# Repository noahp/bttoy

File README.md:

bttoy
=====
Bluetooth robot toy.

Parts
=====
1A/40V schottky  
http://www.mouser.com/ProductDetail/AVX/SD1206T040S1R0/?qs=sGAEpiMZZMtQ8nqTKtFS%2fB%252bvZQIExTNLVUxpicOfnng%3d

47uF electrolytic, 5x5.2mm  
http://www.mouser.com/ProductDetail/Lelon/VE-470M1CTR-0505/?qs=sGAEpiMZZMvwFf0viD3Y3dptsVif%2fXhRiPinzX%2fdZgo%3d

inductor  
http://www.mouser.com/ProductDetail/Bourns/SRN4012T-100M/?qs=sGAEpiMZZMsg%252by3WlYCkUz9C2LVsYPGHqSjhQBKaWDQ%3d

switch  
http://www.mouser.com/ProductDetail/Apem/MHSS1105/?qs=sGAEpiMZZMtHXLepoqNyVYxFoZ6bbHER8MOeX4eGSrE%3d

motor ic  
http://www.mouser.com/ProductDetail/ON-Semiconductor/LV8548MC-AH/?qs=sGAEpiMZZMuleuVm2ofeX1ZeyMQNcmgu

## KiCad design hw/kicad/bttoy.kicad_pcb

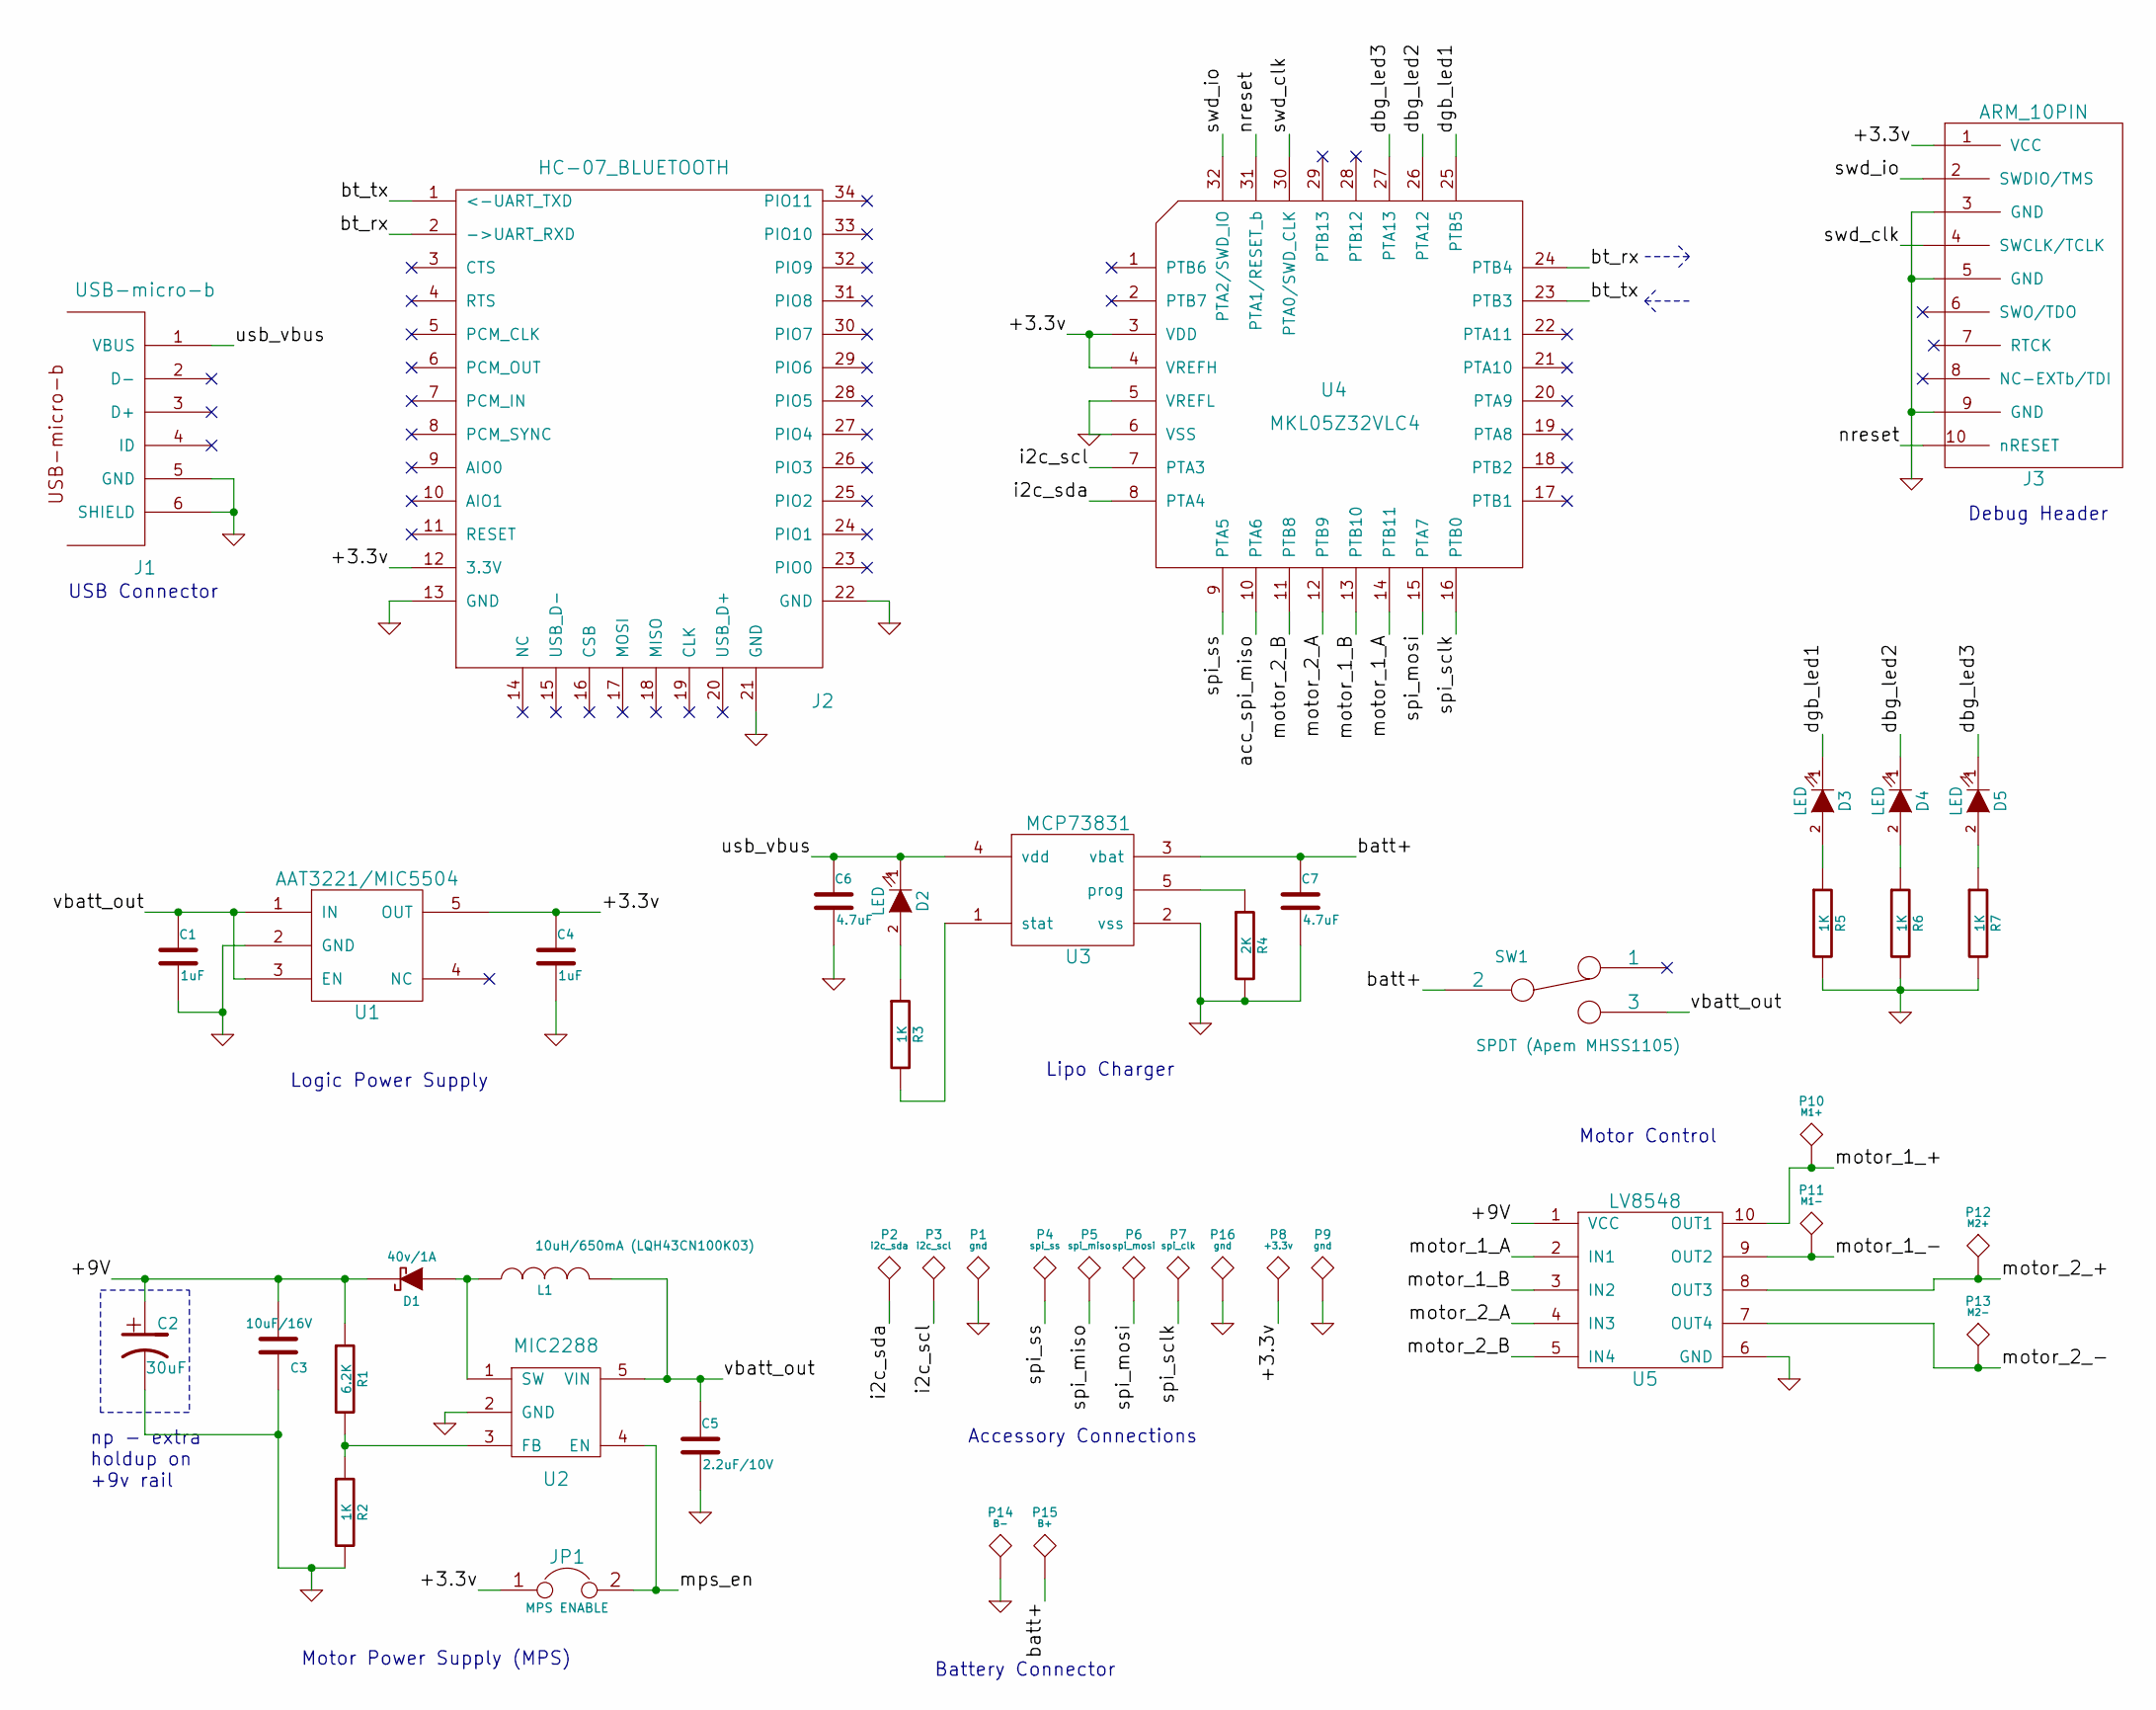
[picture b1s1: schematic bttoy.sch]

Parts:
C1, C4: 1uF; SMD_0603_R
C2: 30uF; SMD_5X5.2_CAP
C3: 10uF/16V; SMD_0805_R
C5: 2.2uF/10V; SMD_0603_R
C6, C7: 4.7uF; SMD_0603_R
D1: 40v/1A; SMD_1206_DIODE
D2, D3, D4, D5: LED; SMD_0603_LED
J1: USB-micro-b; usb_micro_b_smt
J2: HC-07_BLUETOOTH; HC-07_bluetooth
J3: ARM_10PIN; ARM_10_PIN_SMT
JP1: MPS ENABLE; jmp_small
L1: 10uH/650mA (LQH43CN100K03); SMD_4x4_INDUCTOR
P1, P9, P16: gnd; TEST_0.100
P2: i2c_sda; TEST_0.100
P3: i2c_scl; TEST_0.100
P4: spi_ss; TEST_0.100
P5: spi_miso; TEST_0.100
P6: spi_mosi; TEST_0.100
P7: spi_clk; TEST_0.100
P8: +3.3v; TEST_0.100
P10: M1+; TEST_0.100
P11: M1-; TEST_0.100
P12: M2+; TEST_0.100
P13: M2-; TEST_0.100
P14: B-; TEST_0.100
P15: B+; TEST_0.100
R1: 6.2K; SMD_0603_R
R2, R3, R5, R6, R7: 1K; SMD_0603_R
R4: 2K; SMD_0603_R
SW1: SPDT (Apem MHSS1105); TH_APEM_MHSS1105_SPDT
U1: AAT3221/MIC5504; SMD_SOT23-5
U2: MIC2288; SMD_SOT23-5
U3: MCP73831; SMD_SOT23-5
U4: MKL05Z32VLC4; SMD_LQFP-32
U5: LV8548; SMD_SOIC-10NB

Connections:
/+3.3v: C4.1, J2.12 (3.3V), J3.1 (VCC), JP1.1, P8.1, U1.5 (OUT), U4.3 (VDD), U4.4 (VREFH)
/+9V: C2.1, C3.1, D1.2 (K), R1.1, U5.1 (VCC)
/batt+: C7.1, P15.1, SW1.2, U3.3 (vbat)
/bt_rx: J2.2 (->UART_RXD), U4.24 (PTB4)
/bt_tx: J2.1 (<-UART_TXD), U4.23 (PTB3)
/dbg_led2: D4.1 (K), U4.26 (PTA12)
/dbg_led3: D5.1 (K), U4.27 (PTA13)
/dgb_led1: D3.1 (K), U4.25 (PTB5)
/i2c_scl: P3.1, U4.7 (PTA3)
/i2c_sda: P2.1, U4.8 (PTA4)
/motor_1_+: P10.1, U5.10 (OUT1)
/motor_1_-: P11.1, U5.9 (OUT2)
/motor_1_A: U4.14 (PTB11), U5.2 (IN1)
/motor_1_B: U4.13 (PTB10), U5.3 (IN2)
/motor_2_+: P12.1, U5.8 (OUT3)
/motor_2_-: P13.1, U5.7 (OUT4)
/motor_2_A: U4.12 (PTB9), U5.4 (IN3)
/motor_2_B: U4.11 (PTB8), U5.5 (IN4)
/mps_en: JP1.2, U2.4 (EN), U4.17 (PTB1)
/nreset: J3.10 (nRESET), U4.31 (PTA1/RESET_b)
/spi_mosi: P6.1, U4.15 (PTA7)
/spi_sclk: P7.1, U4.16 (PTB0)
/spi_ss: P4.1, U4.9 (PTA5)
/swd_clk: J3.4 (SWCLK/TCLK), U4.30 (PTA0/SWD_CLK)
/swd_io: J3.2 (SWDIO/TMS), U4.32 (PTA2/SWD_IO)
/usb_vbus: C6.1, D2.1 (K), J1.1 (VBUS), U3.4 (vdd)
/vbatt_out: C1.1, C5.1, L1.2, SW1.3, U1.1 (IN), U1.3 (EN), U2.5 (VIN)
GND: C1.2, C2.2, C3.2, C4.2, C5.2, C6.2, C7.2, J1.5 (GND), J1.6 (SHIELD), J2.13 (GND), J2.21 (GND), J2.22 (GND), J3.3 (GND), J3.5 (GND), J3.9 (GND), P1.1, P9.1, P14.1, P16.1, R2.2, R4.2, R5.2, R6.2, R7.2, U1.2 (GND), U2.2 (GND), U3.2 (vss), U4.5 (VREFL), U4.6 (VSS), U5.6 (GND)
unnamed: D1.1 (A), L1.1, U2.1 (SW)
unnamed: D2.2 (A), R3.1
unnamed: D3.2 (A), R5.1
unnamed: D4.2 (A), R6.1
unnamed: D5.2 (A), R7.1
unnamed: R1.2, R2.1, U2.3 (FB)
unnamed: R3.2, U3.1 (stat)
unnamed: R4.1, U3.5 (prog)

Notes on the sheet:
Lipo Charger
Logic Power Supply
Debug Header
USB Connector
Motor Power Supply (MPS)
np - extra holdup on +9v rail
Motor Control
Accessory Connections
Battery Connector

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
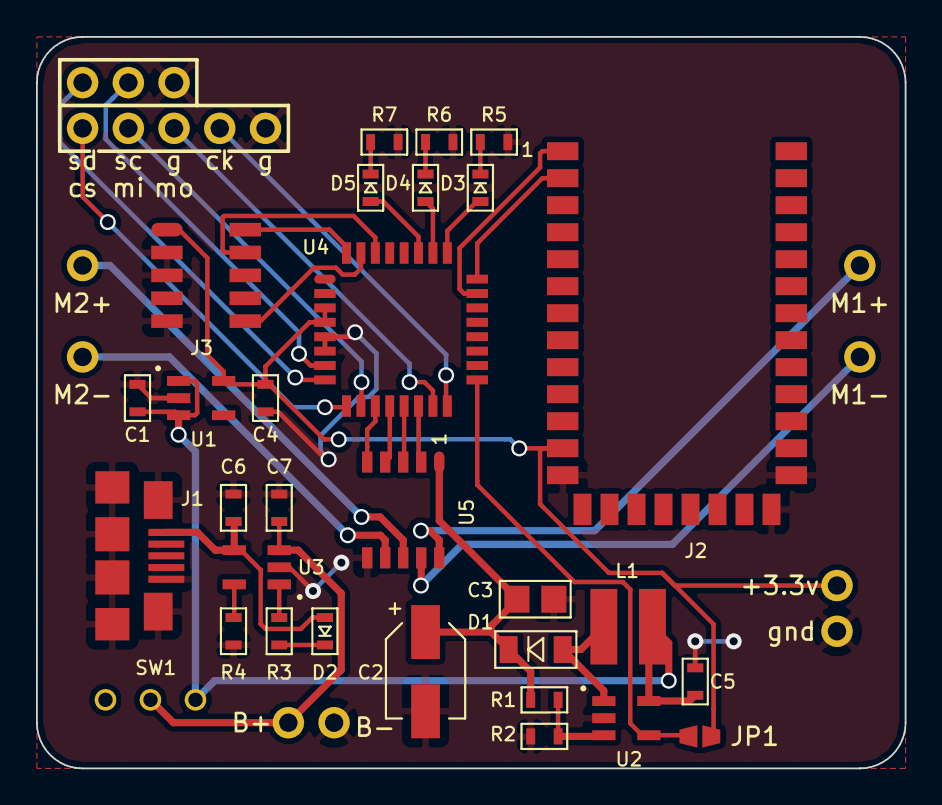
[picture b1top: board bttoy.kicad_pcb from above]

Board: 2 copper layers, 48.3 x 40.6 mm, 46 parts (0 on the bottom side), 37 nets.

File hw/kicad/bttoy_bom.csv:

Value,Ref,Footprint
MKL05Z32VLC4,U4,kicadlib:SMD_LQFP-32
MCP73831,U3,kicadlib:SMD_SOT23-5
USB-micro-b,J1,kicadlib:usb_micro_b_smt
AAT3221/MIC5504,U1,kicadlib:SMD_SOT23-5
1K,R3,kicadlib:SMD_0603_R
4.7uF,C6,kicadlib:SMD_0603_R
LED,D2,kicadlib:SMD_0603_LED
2K,R4,kicadlib:SMD_0603_R
4.7uF,C7,kicadlib:SMD_0603_R
1uF,C1,kicadlib:SMD_0603_R
1uF,C4,kicadlib:SMD_0603_R
ARM_10PIN,J3,kicadlib:ARM_10_PIN_SMT
HC-07_BLUETOOTH,J2,kicadlib:HC-07_bluetooth
MIC2288,U2,kicadlib:SMD_SOT23-5
10uH/650mA (LQH43CN100K03),L1,kicadlib:SMD_4x4_INDUCTOR
2.2uF/10V,C5,kicadlib:SMD_0603_R
10uF/16V,C3,kicadlib:SMD_0805_R
40v/1A,D1,kicadlib:SMD_1206_DIODE
6.2K,R1,kicadlib:SMD_0603_R
1K,R2,kicadlib:SMD_0603_R
MPS ENABLE,JP1,kicadlib:jmp_small
SPDT (Apem MHSS1105),SW1,kicadlib:TH_APEM_MHSS1105_SPDT
30uF,C2,kicadlib:SMD_5X5.2_CAP
LV8548,U5,kicadlib:SMD_SOIC-10NB
M1+,P10,kicadlib:TEST_0.100
M1-,P11,kicadlib:TEST_0.100
M2+,P12,kicadlib:TEST_0.100
M2-,P13,kicadlib:TEST_0.100
+9V_DBG,P1,kicadlib:TEST_0.100
LED,D3,kicadlib:SMD_0603_LED
1K,R5,kicadlib:SMD_0603_R
LED,D4,kicadlib:SMD_0603_LED
1K,R6,kicadlib:SMD_0603_R
LED,D5,kicadlib:SMD_0603_LED
1K,R7,kicadlib:SMD_0603_R
spi_mosi,P6,kicadlib:TEST_0.100
spi_miso,P5,kicadlib:TEST_0.100
spi_ss,P4,kicadlib:TEST_0.100
spi_clk,P7,kicadlib:TEST_0.100
i2c_sda,P2,kicadlib:TEST_0.100
i2c_scl,P3,kicadlib:TEST_0.100
+3.3v,P8,kicadlib:TEST_0.100
gnd,P9,kicadlib:TEST_0.100
B-,P14,kicadlib:TEST_0.100
B+,P15,kicadlib:TEST_0.100

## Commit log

2014-11-26 - add kicad project, just schematic for now
2014-11-26 - add kicadlib submodule
2014-12-02 - add libs
2014-12-22 - start basic schematic, few ic's
2015-02-27 - start flushing out subsystems
2015-03-02 - flesh out schematic, add MPS using MIC2288 boost controller
2015-03-02 - add reference part # for inductor
2015-03-02 - change high side switches to pfet
2015-03-08 - remove sub schematic, replace discrete motor control with LV8548 IC
2015-03-08 - add motor connectors
2015-03-08 - fill out motor control subsystem
2015-03-09 - new version of kicalib
2015-03-14 - update to latest kicadlib
2015-03-14 - more work on schematic
2015-03-14 - more schematic work
2015-03-14 - add netlist
2015-03-14 - start layout
2015-03-14 - add link to lv8548 on mouser
2015-04-01 - new version of kicadlib with bom generator script
2015-04-01 - update to fixed hc-07 bluetooth footprint
2015-04-12 - connect motor control signals
2015-04-18 - add bom, add acc. connections, reload parts on pcb
2015-04-21 generate netlist and cmp assoc.
2015-04-21 tune up schematic a bit more, and start positioning footprints on pcb
2015-04-25 mps and dbg led's laid out
2015-05-10 arrange footprint groups in pcb, change position of power switch to control all batt output
2015-08-10 update submodule to fix lqfp-32 footprint
2015-09-14 place test points
2015-09-14 gerbers and done
